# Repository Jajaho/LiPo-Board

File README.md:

# Battery Management and Boost Converter Board

This PCB combines a single cell 3.7 V LiPo-battery charger and protection circuitry with a 5 V boost converter to deliver up to 1 A of current for small projects.
The main components are:
- **TP4056** 1 A standalone linear Li-Ion battery charger with thermal protection in SOP-8 package
- **MT3608** High efficiency 1.2 MHz 2 A boost converter

You can check out the post on my website [here](https://jajaho.github.io//projects/lipo_booster_charger) if you like.

## Repository Contents

The project was originally designed and manufactured in 01/2019 using Eagle ECAD. Later they have been converted to KiCad to preserve them. 
The KiCad design files represent the original files as closely as possible.

- `src/eagle-2019` - The original design files which produced the production files of the manufactured PCB.
- `src/kicad-2019` - Converted design files which produced the production files of the manufactured PCB.

The original production files are archived in `outputs/LiPo-BoardV1_2019-01-18.zip`.
Reexporting `src/eagle-2019` to gerber using the `template_2_layer.cam` in the modern Autodesk Fusion 2705.1.25 x86_64 today produces very similar geometry, expcept for the  ground pad spokes are 0.25 mm (10 mil) wide instead of 20 mil in the original files and the clearance corners are chamfered instead of rounded.
`src/kicad-2019` needed some hand adjustments aswell. Trace clearances, board clearance and copper pour nets where wrong after the automatic import. It is now mostly correct.

The faulty wiring of the enable switch was discovered only after the board has been manufactured. Consequently this mistake has been corrected in the schematic but the board has not been rerouted.

- `src/eagle` - A later state of the design files, with incomplete routing after the DPST switch was rewired.
- `src/kicad` - A later state of the converted design files, with incomplete routing after the DPST switch was rewired.

Schematic PDFs of both KiCad projects are available in the generated `schematic-pdfs` artifact.

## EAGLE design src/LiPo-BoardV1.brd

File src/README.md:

# Source files
The project was originally designed in Eagle ecad but has been converted to KiCad. The original Eagle files are in the `eagle` directory.  

The kicad pcb is unrouted however.

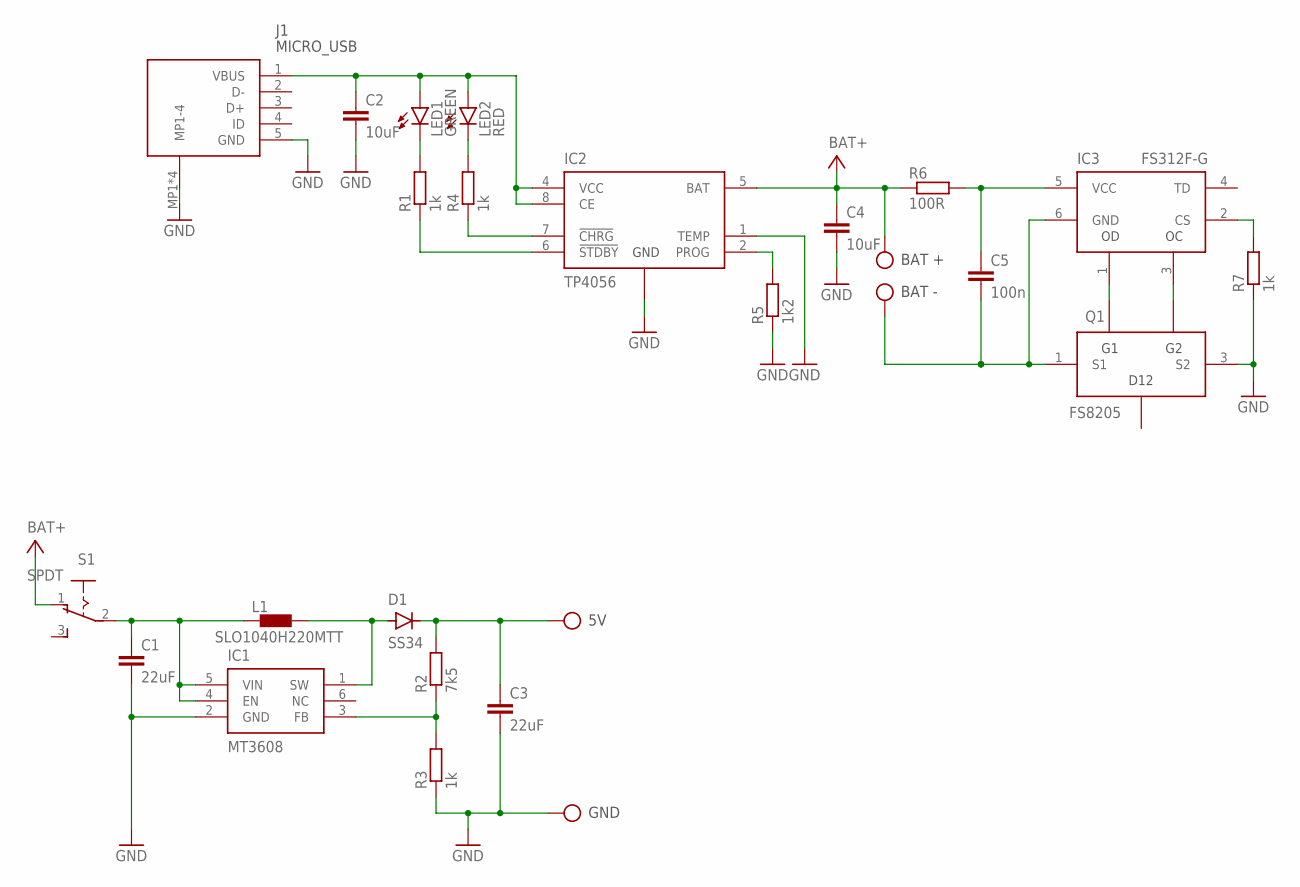
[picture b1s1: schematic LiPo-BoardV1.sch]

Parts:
C1, C3: 22uF; C1812
C2, C4: 10uF; C0603
C5: 100n; C0603
D1: SS34; DO-214AC
IC1: MT3608; SOT-23-6
IC2: TP4056; SOP-8
IC3: FS312F-G; SOT-23-6
J1: MICRO_USB; MICROUSB
J2: 5V; CON-PAD
J3: GND; CON-PAD
J4: BAT +; CON-PAD
J5: BAT -; CON-PAD
L1: SLO1040H220MTT; INDUCTOR10.8X10
LED1: GREEN; CHIPLED_0603
LED2: RED; CHIPLED_0603
Q1: FS8205; SOT-23-6
R1, R3, R4, R7: 1k; R0603
R2: 7k5; R0603
R5: 1k2; R0603
R6: 100R; R0603
S1: SPDT

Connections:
5V: C3.1, D1.C, J2.1, R2.2
BAT+: C4.1, IC2.5 (BAT), J4.1, R6.1, S1.1
BAT-: C5.2, IC3.6 (GND), J5.1, Q1.1 (S1)
GND: C1.2, C2.2, C3.2, C4.2, IC1.2 (GND), IC2.1 (TEMP), IC2.3 (GND), IC2.9 (GND), J1.5 (GND), J1.MP1 (MP1-4), J1.MP2 (MP1-4), J1.MP3 (MP1-4), J1.MP4 (MP1-4), J3.1, Q1.3 (S2), R3.1, R5.1, R7.1
unnamed: D1.A, IC1.1 (SW), L1.2
unnamed: LED1.C, R1.2
unnamed: LED2.C, R4.2
unnamed: IC2.7 (!CHRG), R4.1
unnamed: IC2.6 (!STDBY), R1.1
unnamed: IC1.3 (FB), R2.1, R3.2
unnamed: IC2.2 (PROG), R5.2
unnamed: IC3.1 (OD), Q1.6 (G1)
unnamed: IC3.3 (OC), Q1.4 (G2)
unnamed: IC3.2 (CS), R7.2
unnamed: C5.1, IC3.5 (VCC), R6.2
VBUS: C2.1, IC2.4 (VCC), IC2.8 (CE), J1.1 (VBUS), LED1.A, LED2.A
VIN: C1.1, IC1.4 (EN), IC1.5 (VIN), L1.1, S1.2

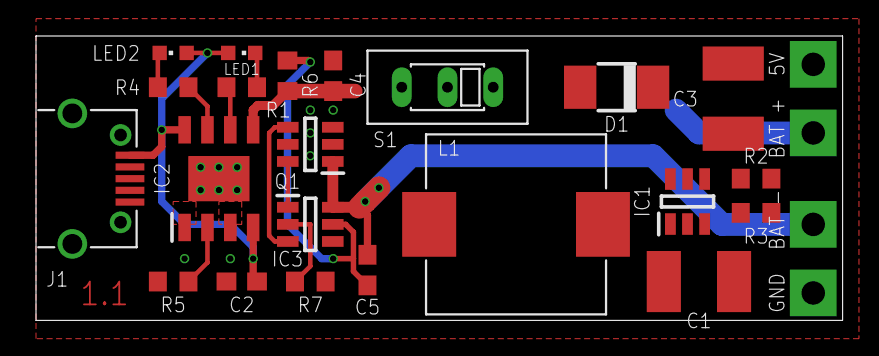
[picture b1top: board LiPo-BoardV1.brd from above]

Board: 2 copper layers, 44.8 x 15.8 mm, 26 parts (0 on the bottom side), 17 nets.

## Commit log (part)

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2023-07-04 Adds project
2023-07-04 Adds gitignore, Removes backup files
2023-07-08 Add kicad project files, restructure folders
2023-07-08 Update kicad schematic
    make it prettier
